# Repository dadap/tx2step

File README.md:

Texas Two Step: A dual axis motor controller for equatorial telescope mounts
============================================================================

![Texas Two Step breadboard prototype controlling an unloaded Orion Astroview]
(https://github.com/dadap/tx2step/raw/master/img/tx2step-breadboard-proto.jpg)

Introduction
------------

The Texas Two Step is a replacement hand controller for the Synta Dual-Axis
motor kit for EQ-3 and EQ-5 type equatorial mounts (it can probably be adapted
to other mount designs utilizing stepper motors as well), with the following
improvements:

* Faster setting rates (original HC is limited to 8x sidereal)
* Analog 2-axis joystick to control setting rates (instead of rate slider switch
  combined with directional pad)
* ST-4 support with independent guiding (ST-4) and setting (joystick) rates.
* Main unit attaches to mount; RA, DEC, ST-4 cables move with telescope, and a
  single cable connects the control unit to a handheld joystick unit.
* Integrated rechargeable battery (to replace 4x D-cell pack, and eliminate the
  additional cable for power)
* All LEDs are dim and red to preserve dark adaptation
* Additional tracking rates (solar, lunar)
* Smaller and lighter
* Lower power draw (current prototype draws about .5 W for tracking)

The Texas Two Step is powered by an Atmel AVR microprocessor (currently an
Atmega328P on a breadboarded prototype circuit) and the stepper motors are
driven by dual TI DRV8834 low-voltage stepper driver ICs. The DRV8834 is
selected to allow a common power source (5V, boosted up from the output of a
single 18650 LiIon cell) for the logic and the motors.

TODO
----

A schematic and PCB layout should eventually be added to this repository.

The following features are not yet implemented:

* Directional switching not implemented; RA tracking direction is dependent on
  the order of stepper motor wiring to the driver boards. The final design is
  intended to allow switching between northern and southern hemisphere operation
  via a DIP switch or jumper setting.

The following features may or may not eventually be implemented:

* Backlash compensation (probably in the declination axis only; RA guiding at
  less than 1x tracking rate requires no backlash compensation.)
* Periodic error correction: implementing this will probably require some form
  of persistent storage, as the available EEPROM storage on the microcontroller
  is likely insufficient.

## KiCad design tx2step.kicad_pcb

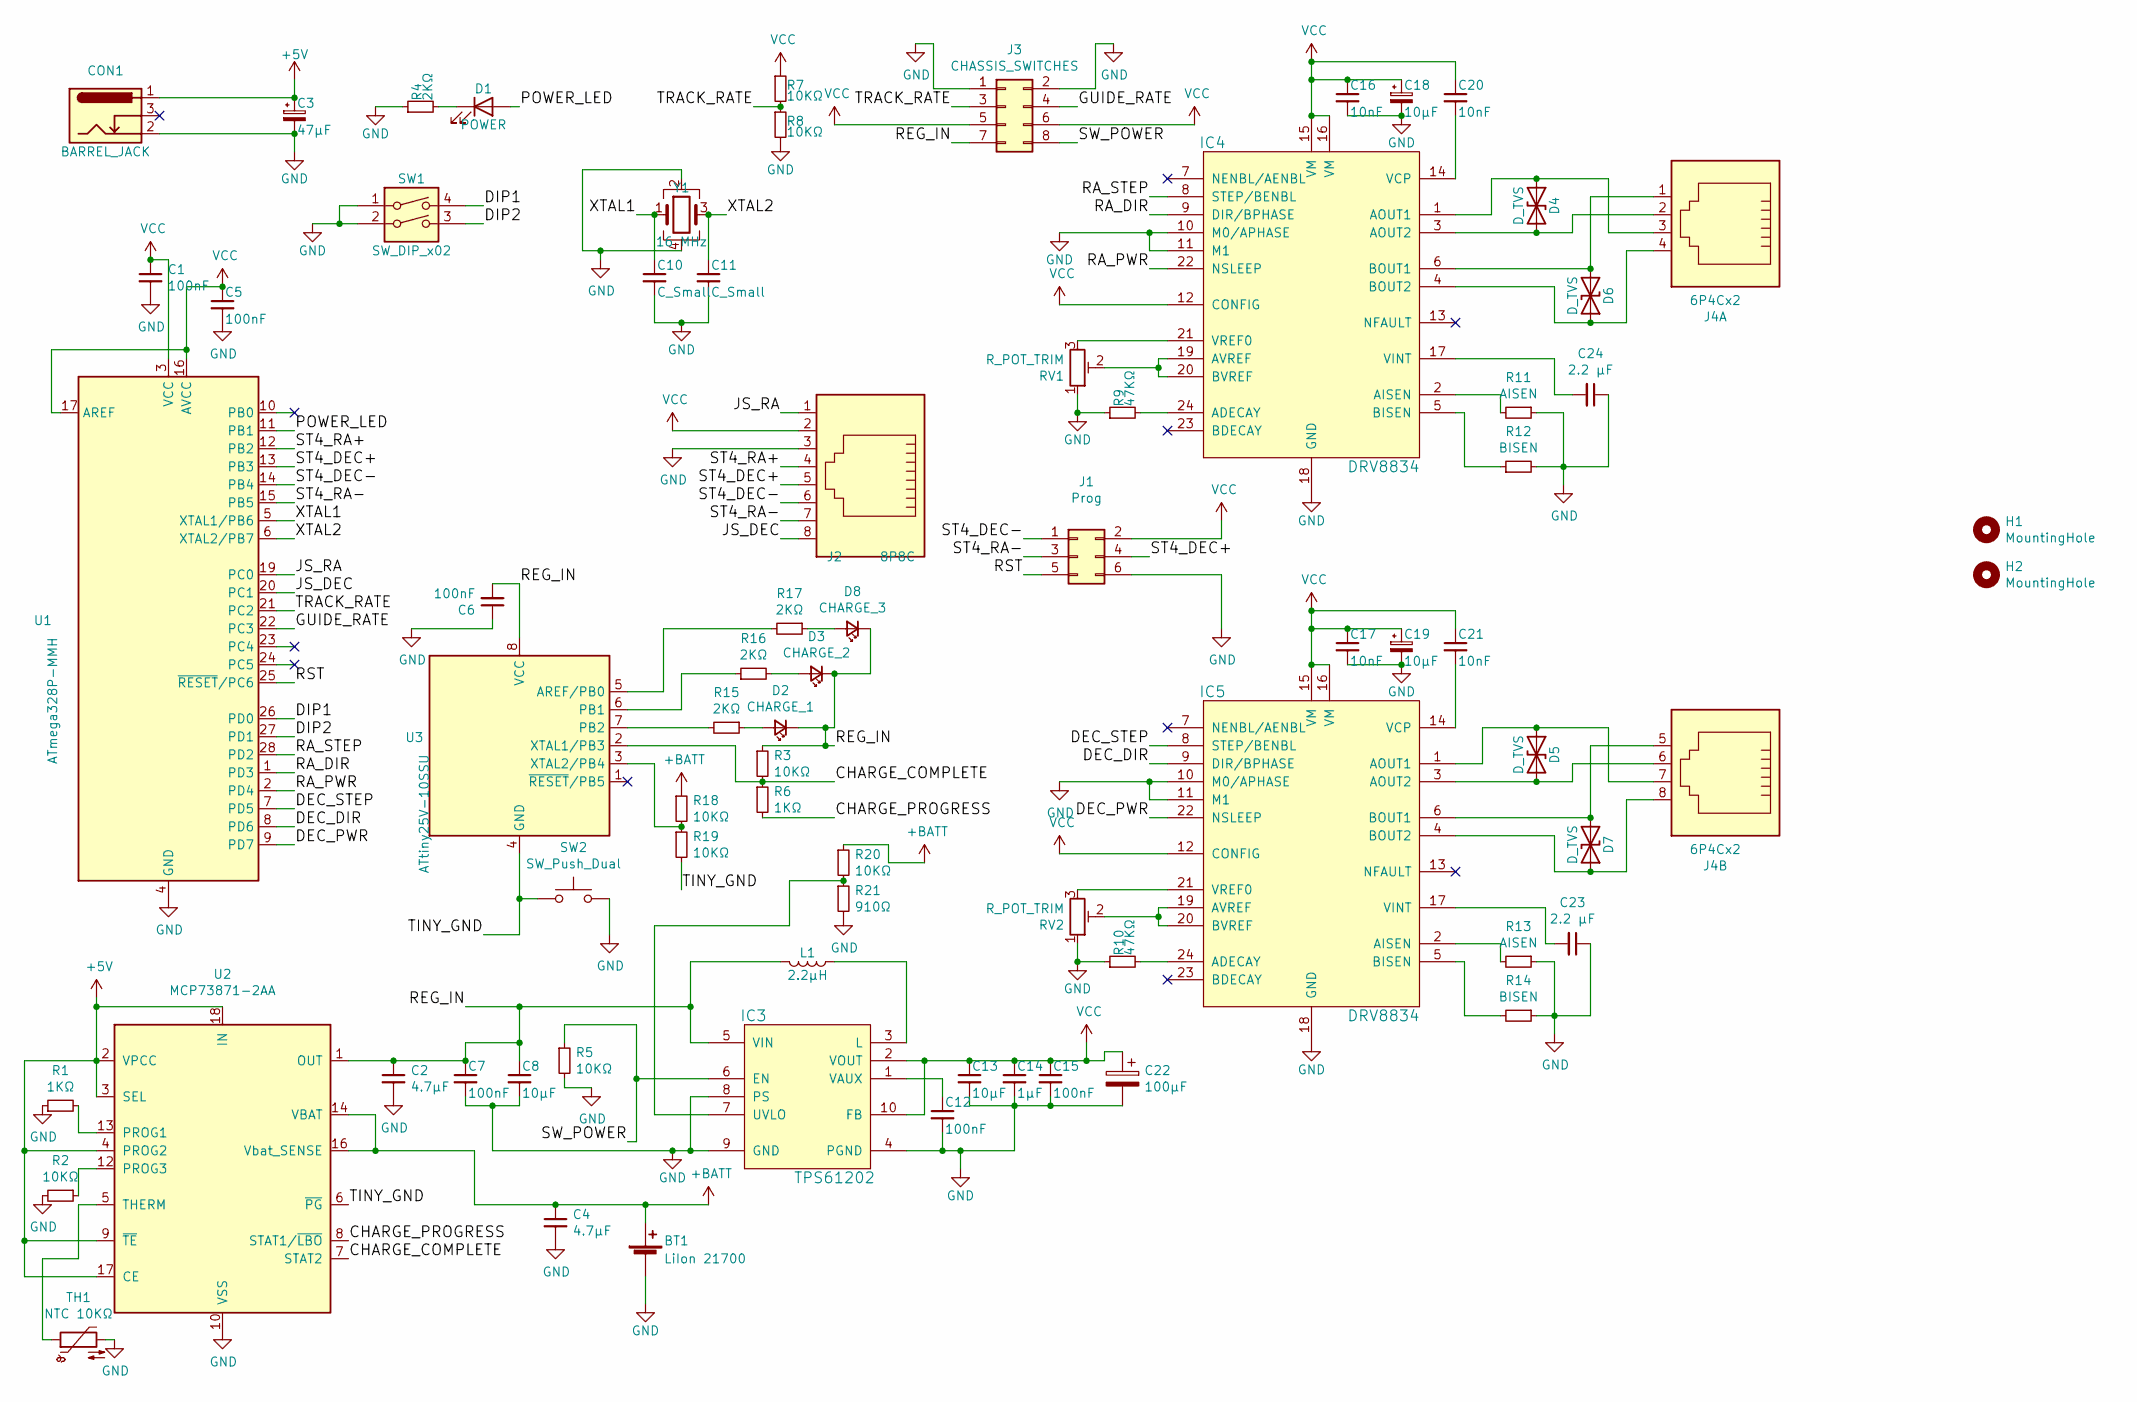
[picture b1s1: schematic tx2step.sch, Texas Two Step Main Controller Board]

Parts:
BT1: LiIon 21700; Battery_Clip_21700
C1, C5, C6, C7, C12, C15: 100nF; C_0603_1608Metric
C2, C4: 4.7µF; C_0603_1608Metric
C3: 47µF; CP_Radial_D5.0mm_P2.00mm
C8, C13, C18, C19: 10µF; C_0805_2012Metric
C10, C11: C_Small; C_0603_1608Metric
C14: 1µF; C_0603_1608Metric
C16, C17, C20, C21: 10nF; C_0603_1608Metric
C22: 100µF; CP_Radial_D5.0mm_P2.00mm
C23, C24: 2.2 µF; C_0603_1608Metric
CON1: BARREL_JACK; BarrelJack_Horizontal
D1: POWER; LED_0603_1608Metric
D2: CHARGE_1; LED_0603_1608Metric
D3: CHARGE_2; LED_0603_1608Metric
D4, D5, D6, D7: D_TVS; D_SOD-323
D8: CHARGE_3; LED_0603_1608Metric
H1, H2: MountingHole; MountingHole_3.2mm_M3
IC3: TPS61202; Texas_S-PVSON-N10_ThermalVias
IC4, IC5: DRV8834; QFN-24-1EP_4x4mm_P0.5mm_EP2.6x2.6mm_ThermalVias
J1: Prog; PinHeader_2x03_P2.54mm_Vertical
J2: 8P8C; RJ45_Amphenol_54602-x08_Horizontal
J3: CHASSIS_SWITCHES; PinHeader_2x04_P2.54mm_Vertical
J4: 6P4Cx2
L1: 2.2µH; L_1008_2520Metric
R1, R6: 1KΩ; R_0603_1608Metric
R2, R3, R5, R7, R8, R18, R19, R20: 10KΩ; R_0603_1608Metric
R4, R15, R16, R17: 2KΩ; R_0603_1608Metric
R9, R10: 47KΩ; R_0603_1608Metric
R11, R13: AISEN; R_0603_1608Metric
R12, R14: BISEN; R_0603_1608Metric
R21: 910Ω; R_0603_1608Metric
RV1, RV2: R_POT_TRIM; Potentiometer_Bourns_TC33X_Vertical
SW1: SW_DIP_x02; DIP-4_W7.62mm
SW2: SW_Push_Dual; SW_SPST_TL3305A
TH1: NTC 10KΩ; R_0402_1005Metric
U1: ATmega328P-MMH; QFN-28-1EP_4x4mm_P0.45mm_EP2.4x2.4mm
U2: MCP73871-2AA; QFN-20-1EP_4x4mm_P0.5mm_EP2.5x2.5mm
U3: ATtiny25V-10SSU; SOIC-8_3.9x4.9mm_P1.27mm
Y1: 16 MHz; Crystal_SMD_3225-4Pin_3.2x2.5mm

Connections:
+5V: C3.1, CON1.1, U2.2 (VPCC), U2.3 (SEL), U2.4 (PROG2), U2.9 (~TE), U2.17 (CE), U2.18 (IN), U2.19 (IN)
+BATT: BT1.1 (+), C4.1, R18.1, R20.1, U2.14 (VBAT), U2.15 (VBAT), U2.16 (Vbat_SENSE)
/CHARGE_COMPLETE: R3.2, R6.1, U2.7 (STAT2), U3.2 (XTAL1/PB3)
/CHARGE_PROGRESS: R6.2, U2.8 (STAT1/~LBO~)
/DEC_DIR: IC5.9 (DIR/BPHASE), U1.8 (PD6)
/DEC_PWR: IC5.22 (NSLEEP), U1.9 (PD7)
/DEC_STEP: IC5.8 (STEP/BENBL), U1.7 (PD5)
/DIP1: SW1.4, U1.26 (PD0)
/DIP2: SW1.3, U1.27 (PD1)
/GUIDE_RATE: J3.4, U1.22 (PC3)
/JS_DEC: J2.8, U1.20 (PC1)
/JS_RA: J2.1, U1.19 (PC0)
/POWER_LED: D1.2 (A), U1.11 (PB1)
/RA_DIR: IC4.9 (DIR/BPHASE), U1.1 (PD3)
/RA_PWR: IC4.22 (NSLEEP), U1.2 (PD4)
/RA_STEP: IC4.8 (STEP/BENBL), U1.28 (PD2)
/REG_IN: C2.1, C6.2, C7.1, C8.1, D2.1 (K), D3.1 (K), D8.1 (K), IC3.5 (VIN), J3.7, L1.2, R3.1, U2.1 (OUT), U2.20 (OUT), U3.8 (VCC)
/RST: J1.5, U1.25 (~RESET~/PC6)
/ST4_DEC+: J1.4, J2.5, U1.13 (PB3)
/ST4_DEC-: J1.1, J2.6, U1.14 (PB4)
/ST4_RA+: J2.4, U1.12 (PB2)
/ST4_RA-: J1.3, J2.7, U1.15 (PB5)
/SW_POWER: IC3.6 (EN), J3.8, R5.1
/TINY_GND: R19.2, SW2.1, U2.6 (~PG~), U3.4 (GND)
/TRACK_RATE: J3.3, R7.2, R8.1, U1.21 (PC2)
/XTAL1: C10.1, U1.5 (XTAL1/PB6), Y1.1
/XTAL2: C11.1, U1.6 (XTAL2/PB7), Y1.3
GND: BT1.2 (-), C1.2, C2.2, C3.2, C4.2, C5.2, C6.1, C7.2, C8.2, C10.2, C11.2, C12.2, C13.2, C14.2, C15.2, C16.2, C17.2, C18.2, C19.2, C22.2, C23.1, C24.1, CON1.2, IC3.4 (PGND), IC3.8 (PS), IC3.9 (GND), IC3.11 (GND), IC4.10 (M0/APHASE), IC4.11 (M1), IC4.18 (GND), IC4.25 (GND), IC5.10 (M0/APHASE), IC5.11 (M1), IC5.18 (GND), IC5.25 (GND), J1.6, J2.3, J3.1, J3.2, R1.1, R2.2, R4.1, R5.2, R8.2, R9.1, R10.1, R11.1, R12.2, R13.1, R14.1, R21.2, RV1.1, RV2.1, SW1.1, SW1.2, SW2.2, TH1.2, U1.4 (GND), U1.18 (GND), U1.29 (GND), U2.10 (VSS), U2.11 (VSS), U2.21 (VSS), Y1.2, Y1.4
unnamed: C12.1, IC3.1 (VAUX)
unnamed: C20.2, IC4.14 (VCP)
unnamed: C21.2, IC5.14 (VCP)
unnamed: C23.2, IC5.17 (VINT)
unnamed: C24.2, IC4.17 (VINT)
unnamed: D1.1 (K), R4.2
unnamed: D2.2 (A), R15.1
unnamed: D3.2 (A), R16.2
unnamed: D4.1 (A1), IC4.1 (AOUT1), J4.3
unnamed: D4.2 (A2), IC4.3 (AOUT2), J4.2
unnamed: D5.1 (A1), IC5.1 (AOUT1), J4.7
unnamed: D5.2 (A2), IC5.3 (AOUT2), J4.6
unnamed: D6.1 (A1), IC4.4 (BOUT2), J4.4
unnamed: D6.2 (A2), IC4.6 (BOUT1), J4.1
unnamed: D7.1 (A1), IC5.4 (BOUT2), J4.8
unnamed: D7.2 (A2), IC5.6 (BOUT1), J4.5
unnamed: D8.2 (A), R17.1
unnamed: IC3.3 (L), L1.1
unnamed: IC3.7 (UVLO), R20.2, R21.1
unnamed: IC4.2 (AISEN), R11.2
unnamed: IC4.5 (BISEN), R12.1
unnamed: IC4.19 (AVREF), IC4.20 (BVREF), RV1.2
unnamed: IC4.21 (VREF0), RV1.3
unnamed: IC4.24 (ADECAY), R9.2
unnamed: IC5.2 (AISEN), R13.2
unnamed: IC5.5 (BISEN), R14.2
unnamed: IC5.19 (AVREF), IC5.20 (BVREF), RV2.2
unnamed: IC5.21 (VREF0), RV2.3
unnamed: IC5.24 (ADECAY), R10.2
unnamed: R1.2, U2.13 (PROG1)
unnamed: R2.1, U2.12 (PROG3)
unnamed: R15.2, U3.7 (PB2)
unnamed: R16.1, U3.6 (PB1)
unnamed: R17.2, U3.5 (AREF/PB0)
unnamed: R18.2, R19.1, U3.3 (XTAL2/PB4)
unnamed: TH1.1, U2.5 (THERM)
VCC: C1.1, C5.1, C13.1, C14.1, C15.1, C16.1, C17.1, C18.1, C19.1, C20.1, C21.1, C22.1, IC3.2 (VOUT), IC3.10 (FB), IC4.12 (CONFIG), IC4.15 (VM), IC4.16 (VM), IC5.12 (CONFIG), IC5.15 (VM), IC5.16 (VM), J1.2, J2.2, J3.5, J3.6, R7.1, U1.3 (VCC), U1.16 (AVCC), U1.17 (AREF)

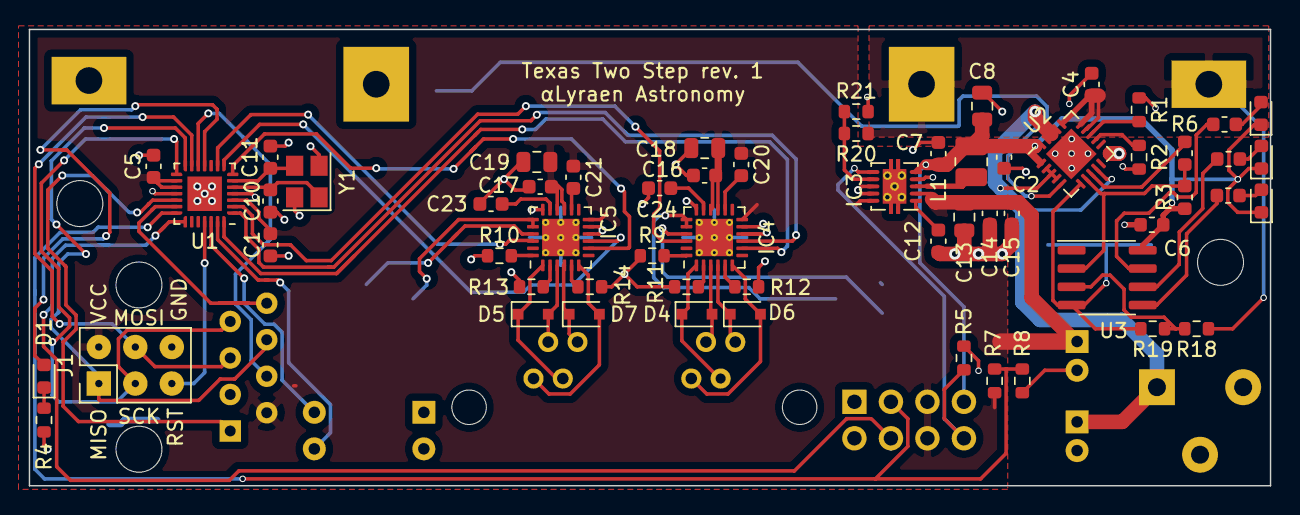
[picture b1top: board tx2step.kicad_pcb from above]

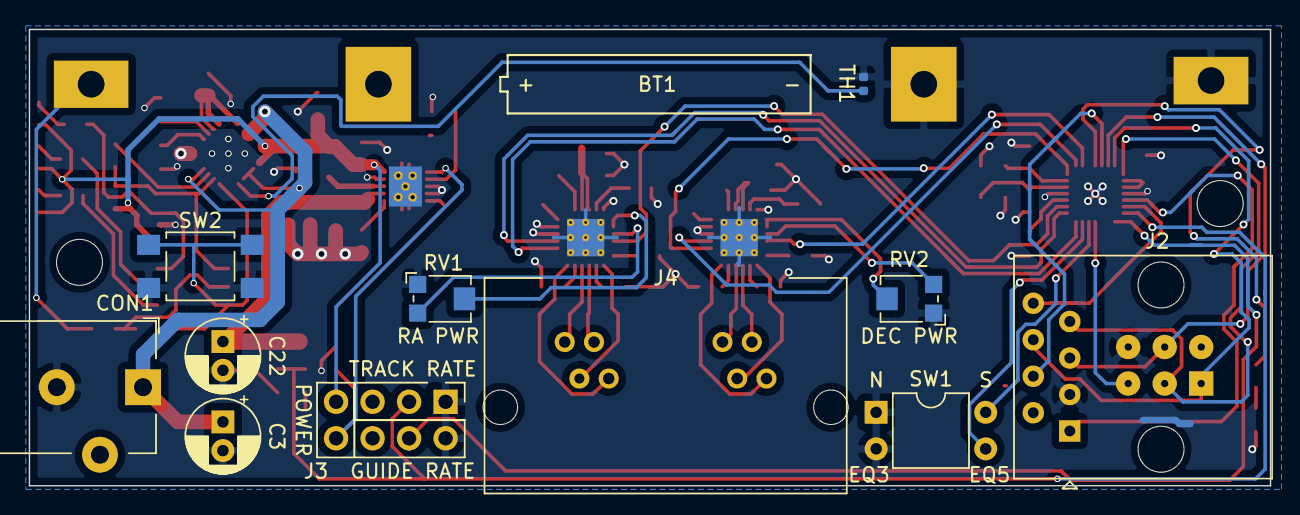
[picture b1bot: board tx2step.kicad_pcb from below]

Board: 2 copper layers, 86.4 x 31.8 mm, 73 parts (12 on the bottom side), 65 nets.

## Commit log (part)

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2017-02-04 Microcontroller code for Texas Two Step, initial commit
    The Texas Two Step is a replacement hand controller for the Synta
    Dual-Axis motor kit for EQ-3 and EQ-5 type equatorial mounts, with
    the following improvements:
    * Faster setting rates (original HC is limited to 8x sidereal)
    * Analog 2-axis joystick to control setting rates (instead of
    rate slider switch combined with directional pad)
2017-02-04 Add potentiometer ranges to axis attributes
    Store the minimum and maximum range of the potentiometer in the axis
    info struct, to allow trimming the joystick. Rearrange the attributes
    within the struct to keep permanent attributes organized separately
    from runtime variables, and use designated initializers so that the
    initial assignment is more self-documenting. The ranges for both axes
    remain [0,1023] until the actual values can be measured.
2017-02-04 Reduce interval between analog reads
    The ADC (bonus fix: correct comment with s/DAC/ADC/) requires a delay
    of 100 *micro*seconds between reads, not 100 *milli*seconds. Polling
    the joystick every 100 microseconds seems somewhat excessive, so drop
    the polling delay from 100ms to 20ms.
2017-02-04 Remove 4µs magic number
    Replace the number "4" with a symbolic constant
2017-02-04 Increase maximum setting speed to 32x
    Testing has demonstrated that RA setting speed can go to 32x before
    stalling: DEC can go a bit faster before stalling out due to gearing,
    but is already going faster because the steps_per_15_degrees value
    fails to take into account the spur gears for the clutch on the DEC
    axis. Expand the range of setting speeds to allow +/- 32x on RA.
2017-02-04 Reclaim unused microstep pins for use as enable
    The DRV8834 drivers are not able to generate sufficient torque when
    microstepping at the low current ceiling (~140 mA) they have been
    configured to chop to. Rather than increase the current and therefore
    the power consumption, just abandon the idea of microstepping, since
    RA tracking at 1x sidereal rate is already in the neighborhood of 10Hz
    anyway. Since the microstep control pins are now hardwired, they can
2017-02-17 Add preprocessor check for clock speed
    The accuracy of micros() is limited by an integer division of 64 by the
    clock rate in hertz divided by one million. Since the AdaFruit Pro Trinket
    originally used to prototype this project runs at 12 MHz, this rounded the
    value 64/12 down from 5 1/3 to 5, causing inaccuracy in the tracking rate.
    The current prototype is a standalone Atmega328 on a breadboard, clocked
    at 12 MHz to match the original 3.3V Pro Trinket prototype. Add a check at
2017-02-17 Always leave RA enabled
    This frees up a pin, and allows all of the motor control output pins to
    live on the same side of the MCU. RA is rarely disabled; this only
    happens if setting or guiding at 1x sidereal in the opposite direction
    of RA.
2017-02-17 Wait 1ms after enabling motor
    The DRV8834 datasheet specifies a 1ms minimum time between waking up the
    driver and stepping. The RA axis currently intermittently does not work,
    but can be recovered by unplugging the jumper from the enable pin on the
    driver board to Vcc and plugging it back in again; add a 1ms delay after
    enabling the driver in case the missing delay is responsible for this
    intermittent failure.
2017-02-21 Add support for multiple setting rates
    Assign an additional analog pin to read a switch (SPDT on-off-on, read
    common pin which is tied to a pair of voltage dividing resistors) to
    set the tracking rate. Since the number of analog reads is no longer
    the same as the number of axes, refactor the joystick reading code to
    be more generic analog reading code and decouple it from the axes.
    The us_per_15_degrees values are based upon a sidereal day of 23h 56m
2017-02-21 Only perform debug prints when input values change.
    Now that debug prints are less voluminous, enable debug printing on
    the serial line by default for now.
2017-02-21 Put opening curly braces of functions on their own lines
    Stylistic preference
2017-02-21 Set analog sensor pin input mode when initializing
    Things seem to work without doing so explicitly, but it's probably good
    to be explicit, anyway.
2017-02-21 Fix comments regarding tracking rates
    The tracking rate is no longer fixed to sidereal time, so adjust all
    comments referring to sidereal time to be more generic. Also correct
    inverted units to 4x instead of 1/4.
2017-02-21 Add README and .gitignore
2017-02-21 Make analog_sensor::affects_tracking const
    This value never changes per sensor, so it should be constant.
    Also add comments denoting the delineation between permanent and
    runtime attributes, similar to the ones in the axis struct definition.
2017-02-22 Fix rate units in comments
    Partially revert commit 49c4de7cf976f975a3846f1d6528e56ce28cea5f, which
    incorrectly "corrected" the 1/4 to 4x in comments describing the units
    that tracking/setting/guiding rates are expressed in. 1/4 is correct,
    as one *unit* represents 25% of the tracking rate.
2017-02-22 Don't bother catching up on missed steps at high speeds
    Catching up on missed steps mostly makes sense when attempting to track
    precisely at a fixed rate. The precision is less important when setting
    or guiding, and missed steps are more likely at higher speeds, so don't
    bother trying to catch up on missed steps when stepping faster than 50
    steps per second to hopefully smooth out stuttering at high speeds.
2017-02-22 Break sensor reading out of per-axis loop
    There's no intrinsic relationship between reading sensors and the
    number of axes any more, so take the read_analog_sensor() call out of
    the NUM_AXES loop.
2017-02-24 Remove short_name field from axis struct
    This isn't used any more by the current debug print code.
2017-02-25 Add LICENSE file
    Also add a newline between the project name and the copyright line in
    the comment at the top of tx2step.ino.
2017-02-25 Add support for ST-4 guiding
    Assign pins 10 through 13 for ST-4, and add code to debounce ST-4
    input and adjust the rate based on the combination of ST-4 input and
    the guiding rate set by the GUIDING_RATE potentiometer. Pins 10 through
    13 are selected because pins 11 through 13 are used for SPI; pin ST-4
    pin 3 will be connected to pin 10 when the controller is on, and to
    RESET when the controller is off, to allow for reprogramming the
2017-02-28 Initial WIP schematic
    Add a partial Kicad schematic for the Texas Two Step. For now, only the
    three main ICs (Atmega328P, 2x DRV8834) and a handful of supporting
    components are present.
2017-02-28 Resize schematic to US Letter
2017-03-01 Remove pullup resistor on RESET
    There won't be a physical reset button, and ISP seems to work fine
    without the pullup.
2017-03-01 Create separate logic supply
    The main microcontroller IC may be powered directly from the DC barrel
    jack when power to the rest of the system is shut down. AREF is left
    connected to the main voltage rail.
2017-03-01 Share bypass capacitor for VCC and AVCC
2017-03-02 Fix errors in DRV8834 component
    Add missing pins, remap misnumbered pins
2017-03-02 Rename drv8834.lib to tx2step.lib
    There will be a number of other components used in this project which
    are not currently in any of the kicad libraries; rename the drv8834
    library to reflect the project name, so that all of the custom
    components can share a single library.
2017-03-02 Move DRV8834 label to corner
2017-03-02 Add rate selector switches
2017-03-02 Add clock crystal
2017-03-02 Add additional power ICs
    TPS2113A power multiplexer and TPS61202 boost converter.
    Not wired up yet.
2017-03-02 Connect MCP73831 and battery
2017-03-02 Connect DC in and battery to multiplexer
    The DC in source will take priority. Also connect the charge state LED.
2017-03-02 Wire up TPS61202 boost regulator and power side of DPDT switch
    The power supply circuit should now be complete.
2017-03-02 Add DIP switch for settings
    All of the pins on the MCU are now occupied!
2017-03-02 Add project info to schematic
2017-03-02 Add power LED
2017-03-02 Connect error LEDs to DRV8834s
    Also give the other two LEDs names
2017-03-02 Generate initial netlist
2017-03-02 Add NC flags to all remaining unconnected pins
    Also fix broken connection to a capacitor
2020-10-27 Remap symbols to new format
2020-10-27 Fix barrel jack connection
    GND was connected to wrong barrel jack pin. Connect to both the
    sleeve (pin 2) and the switch (pin 3) as we don't actually use
    the switch functionality.
2020-10-27 Use unshielded jacks
    Reduces number of NC pins
2020-10-27 Simplify DRV8834 current limit configuration
    Wire A/B VREF directly to VREFO and connect the ISEN pins to a
    resistor network. The current limiting can be adjusted by swapping
    the resistor value.
2020-10-27 Use DC jack switch for LED
    Repurpose power LED for use as a "running on battery" indicator.
    If the unit is running while plugged in, the charge indicator will
    indicate power.
2020-10-28 Use labeled nets
    Clean up the schematic by using labeled nets between the ucontroller
    and other components. Also remove the pin to the power switch, as
    the microcontroller is no longer powered when the power switch is
    off, and reuse it to detect whether the DC connector is plugged in.
2020-10-28 Replace switches with pin header
    This allows the switches to be mounted on the chassis, freeing up
    space on the board and allowing for component flexibility.
2020-10-28 Delete rescue lib
    Remap all symbols to proper libraries
2020-11-03 Add hidden thermal pad pins to IC schematics
2020-11-03 Use multi-part component for combined 6P4C jack
2020-11-08 Update footprints from BOM
2020-11-08 Add separate bypass capacitors for AVR VCC/AVCC
    They're on opposite sides of the chip and should probably each
    have their own bypass
2020-11-10 Initial PCB layout
2020-11-17 Use trimpots to adjust current clamping
    It turns out resistor networks aren't available in a wide variety of
    values. Replace the resistor network with fixed value resistors and
    add trimpots for each axis to adjust the current clamping.
2020-11-18 Add more power planes
2020-11-18 Rotate DIP switch
2020-11-18 Update silkscreen revision ID
2020-11-20 Clean up tracks
2020-11-20 Rotate switch headers
2020-11-21 more rerouting and cleanup
2020-11-24 Improve DRV8845 xISEN resistor courtyard clearances; fully connect thermal pads
2020-11-24 Use smaller footprint for THT capacitor
2021-01-01 move silkscreen to avoid collision
2021-01-01 move isen; use pulldown
2021-01-01 isp pads pogo only
    No need to access these pads from the other side, where they're
    covered by the 8P8C connector, which doesn't leave room for
    soldering through-hole headers.
2021-01-01 Fix AVR bypass capacitor values
2021-01-01 connect drv8834 CONFIG directly to VCC
2021-01-01 add large bulk capacitor on vcc
2021-01-01 bump silkscreen rev
2021-01-01 Restore capacitors on DRV8834 VINT
    This pin still needs a capacitor even if it's not being used to
    supply the CONFIG pin.
2021-01-01 Delete driver error LEDs
    They don't actually seem particularly useful
2021-01-01 fix minor clearance issues
2021-01-05 Add separate uC for charge status LEDs
2021-01-05 Add resistor divider to TPS61202 UVLO pin
2021-01-05 Reverse trimpot pins
    Make clockwise increase the ILIM voltage
2021-01-07 Use mega328-driven LED for non-charge status
    Now that we have a separate uC for the charge progress/status LEDs,
    repurpose the existing LED to indicate controller reacting to input.

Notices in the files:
tx2step.sch:
© 2017 Daniel Dadap, αLyraen Astronomical Products
